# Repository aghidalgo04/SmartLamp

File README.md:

# SmartLamp: Embedded Environmental Control System

**SmartLamp** is a comprehensive embedded system designed to monitor study environments and automate lighting and ventilation. It integrates analog and digital sensors with real-time actuation, communicating via a custom UART protocol to a PC interface.

This project demonstrates a full-cycle embedded development process: **Requirements Engineering → SysML Architecture → Hardware Design (PCB) → Firmware Implementation.**

---

## Key Features

* **Real-time Environmental Monitoring:**
    * **Noise Level:** Analog sampling via microphone (categorized as Low/Medium/High) using **Timer 0** interrupts.
    * **Air Quality:** CO2 and TVOC monitoring via **iAQ-Core** (I2C).
    * **Lighting:** Ambient light sensing (Lux) via **VEML7700** (I2C).
    * **Climate:** Temperature and Humidity acquisition (Analog Sensors).
* **Intelligent Actuation:**
    * **Smart Lighting:** Addressable RGB LED strip (SK9822) controlled via **Software SPI** (Bit-banging).
    * **Active Cooling:** DC Fan speed control via **Hardware PWM** (Timer 2).
* **Connectivity:**
    * Robust **UART** communication protocol (9600 baud) with CRC checksums for data integrity.
    * Command-based interface for remote control and telemetry.

---

## Tech Stack & Tools

* **Microcontroller:** Microchip PIC16F886 (8-bit, 20MHz External Oscillator).
* **Firmware Development:** C Language, MPLAB X IDE, XC8 Compiler.
* **Hardware Design:** KiCad (Schematics & PCB Layout).
* **System Modeling:** Eclipse Papyrus (SysML for Block/Activity diagrams).
* **Protocols Implemented:** I2C (MSSP), SPI (Bit-banged), UART (EUSART), PWM (CCP1), ADC.

---

## Repository Structure

The project follows a structured engineering workflow separating development artifacts, documentation, and datasheets.

```text
SmartLamp/
├── Desarrollo/                    # Main Development Directory
│   ├── KiCad/                     # Hardware Design Source
│   │   ├── ProyectoSE.kicad_sch      # Electronic Schematics
│   │   └── ProyectoSE.kicad_pcb      # PCB Layout
│   │   
│   ├── MPLAB/                     # Firmware Source Code
│   │   ├── Code/                  # Application Logic
│   │   │   ├── main.c                # Main Loop & Interrupt Service Routines
│   │   │   └── [Test Files].c        # Unit tests for subsystems
│   │   │
│   │   └── Functions/             # Hardware Abstraction Layer (HAL)
│   │       ├── adc-v1.c/h            # Analog-to-Digital Converter Driver
│   │       ├── i2c-v2.c/h            # I2C Protocol Driver (Hardware MSSP)
│   │       ├── pwm-v1.c/h            # PWM Driver (Timer 2 + CCP)
│   │       ├── spi-master-v1.c/h     # SPI Driver (Software Implementation)
│   │       └── uart-v1.c/h           # UART Driver (Circular Buffer logic)
│   │
│   └── Papyrus/                   # System Architecture Models (UML/SysML)
│
├── Imde-comp/                     # PC Interface Software (Component)
├── Hojas técnicas-20251026/       # Component Datasheets (Sensors/MCU)
└── Documentación/                     # Project Documentation
```

---

## System Architecture

### 1. Firmware Architecture (HAL Approach)
The firmware is designed with modularity in mind. The `main.c` handles the high-level business logic and state management, while the `Functions/` folder contains reusable drivers that abstract the PIC16F886 hardware registers.

* **Interrupt-Driven Sampling:** Noise levels are sampled every 5ms using **Timer 0 (TMR0)** interrupts to ensure non-blocking operation.
* **State Machine:** The UART receiver utilizes a Finite State Machine (FSM) to parse incoming frames byte-by-byte, preventing buffer overflows and handling packet fragmentation.

### 2. Hardware Design (KiCad)
The hardware includes signal conditioning for analog sensors and logic level translation for the communication bus.
* **I2C Bus:** Pull-up resistors configured for 100kHz standard mode.
* **Power:** Regulated 5V rail for logic and separate rail for inductive loads (Fan).

---

## Communication Protocol

Communication between the SmartLamp and the PC is handled via a binary protocol with the following frame structure:

| Header | Length | Command | Payload | CRC (Dummy) |
|:------:|:------:|:-------:|:-------:|:-----------:|
| `0xAA` | 1 Byte | 1 Byte  | N Bytes |   2 Bytes   |

**Command Examples:**
* `0x04`: Set Fan Speed (Payload: 0-100%).
* `0x05`: Set LED Color (Payload: R, G, B, Intensity).
* `0x02`: Read CO2 Level (Response: ppm).

---

## Setup & Installation

### Prerequisites
* **MPLAB X IDE** (v5.xx or higher).
* **XC8 Compiler**.
* **KiCad** (v6.0 or higher) for hardware viewing.

### Build Instructions
1.  Clone the repository:
    ```bash
    git clone [https://github.com/aghidalgo04/SmartLamp.git](https://github.com/aghidalgo04/SmartLamp.git)
    ```
2.  Open **MPLAB X IDE** and import the project from `Desarrollo/MPLAB`.
3.  Ensure the device is set to **PIC16F886** and the toolchain to **XC8**.
4.  Build the project (`Production > Build Project`).
5.  Flash the `.hex` file using a **PICkit 3/4** programmer.

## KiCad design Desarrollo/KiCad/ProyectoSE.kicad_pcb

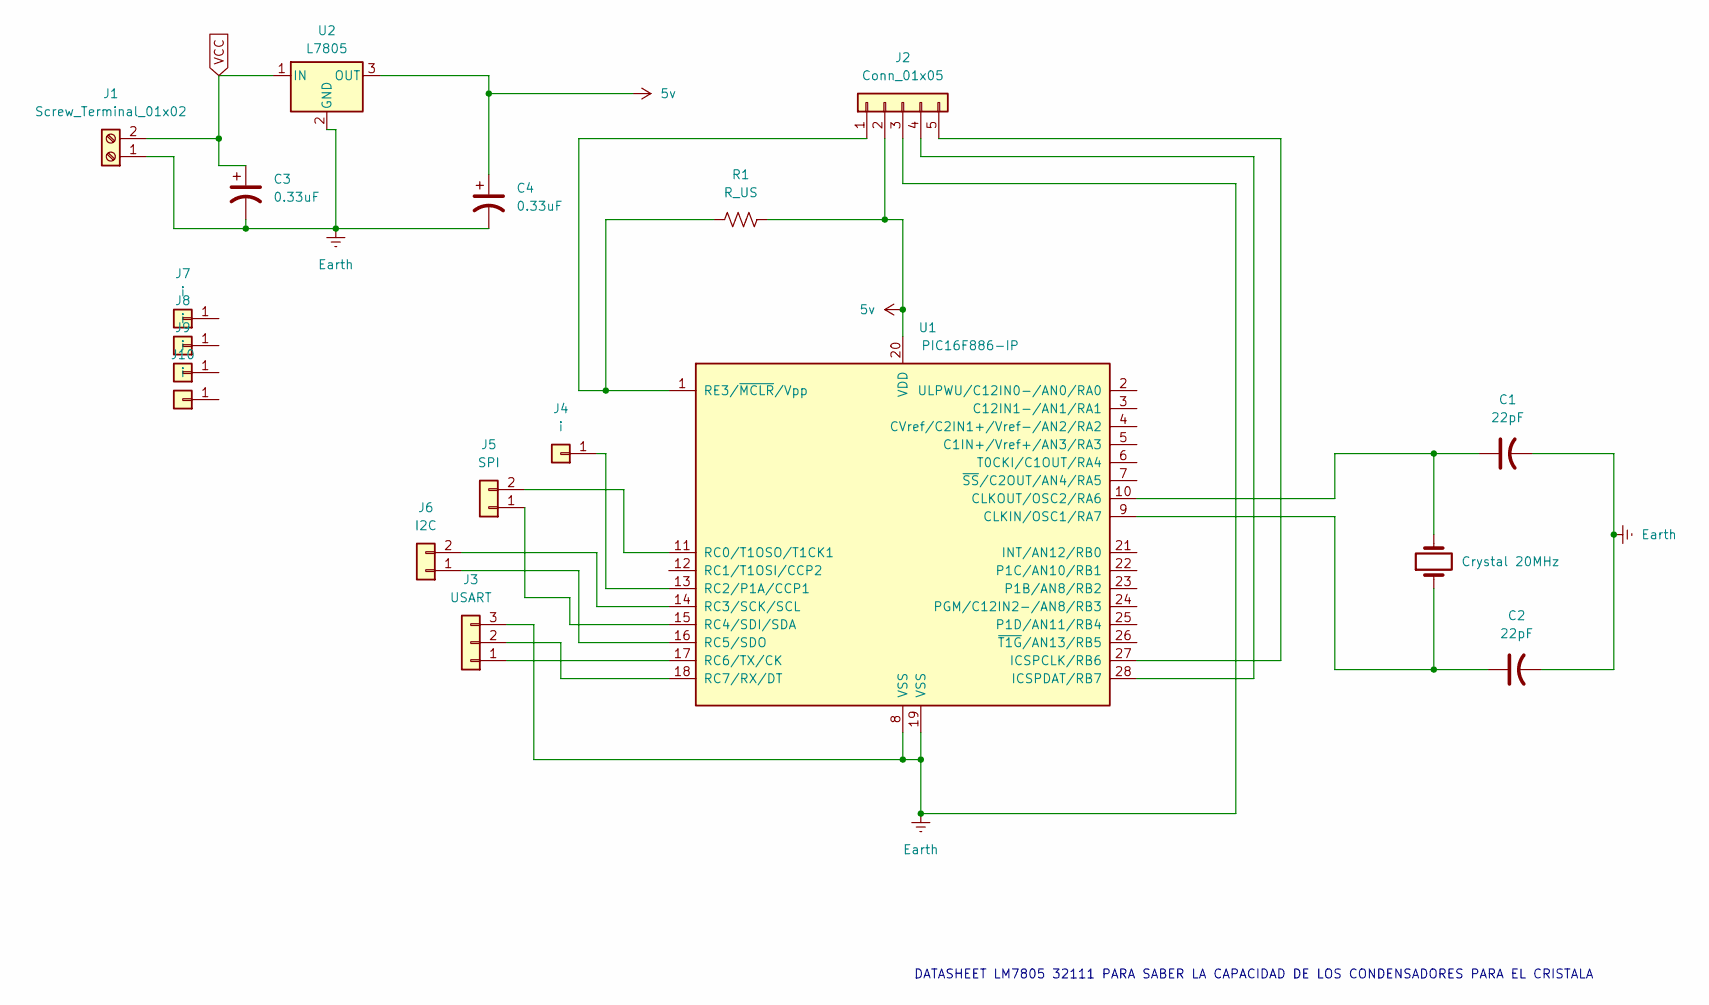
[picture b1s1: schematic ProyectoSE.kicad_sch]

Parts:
C1, C2: 22pF; C_Disc_D7.5mm_W5.0mm_P10.00mm
C3, C4: 0.33uF; C_Disc_D6.0mm_W4.4mm_P5.00mm
J1: Screw_Terminal_01x02; TerminalBlock_Phoenix_MKDS-1,5-2-5.08_1x02_P5.08mm_Horizont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
J2: Conn_01x05; PinHeader_1x05_P2.54mm_Vertical
J3: USART; PinHeader_1x03_P2.54mm_Vertical
J4: i; PinHeader_1x01_P2.54mm_Vertical
J5: SPI; PinHeader_1x02_P2.54mm_Vertical
J6: I2C; PinHeader_1x02_P2.54mm_Vertical
J7, J8, J9, J10: i; MountingHole_4mm_Pad
R1: R_US; R_Axial_DIN0204_L3.6mm_D1.6mm_P7.62mm_Horizontal
U1: PIC16F886-IP; DIP-28_W7.62mm
U2: L7805; TO-220-3_Vertical
Y1: Crystal 20MHz; Crystal_HC49-U_Vertical

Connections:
5v: C4.1, J2.2, R1.2, U1.20 (VDD), U2.3 (OUT)
Earth: C1.2, C2.2, C3.2, C4.2, J1.1, J2.3, J3.3, U1.8 (VSS), U1.19 (VSS), U2.2 (GND)
unnamed: J2.1, R1.1, U1.1 (RE3/~MCLR/Vpp)
unnamed: J2.4, U1.28 (ICSPDAT/RB7)
unnamed: J2.5, U1.27 (ICSPCLK/RB6)
unnamed: J3.1, U1.17 (RC6/TX/CK)
unnamed: J3.2, U1.18 (RC7/RX/DT)
unnamed: J4.1, U1.13 (RC2/P1A/CCP1)
unnamed: J5.1, U1.15 (RC4/SDI/SDA)
unnamed: J5.2, U1.11 (RC0/T1OSO/T1CK1)
unnamed: J6.1, U1.16 (RC5/SDO)
unnamed: J6.2, U1.14 (RC3/SCK/SCL)
unnamed: C2.1, U1.9 (CLKIN/OSC1/RA7), Y1.1
unnamed: C1.1, U1.10 (CLKOUT/OSC2/RA6), Y1.2
VCC: C3.1, J1.2, U2.1 (IN)

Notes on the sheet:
DATASHEET LM7805 32111 PARA SABER LA CAPACIDAD DE LOS CONDENSADORES PARA EL CRISTALA

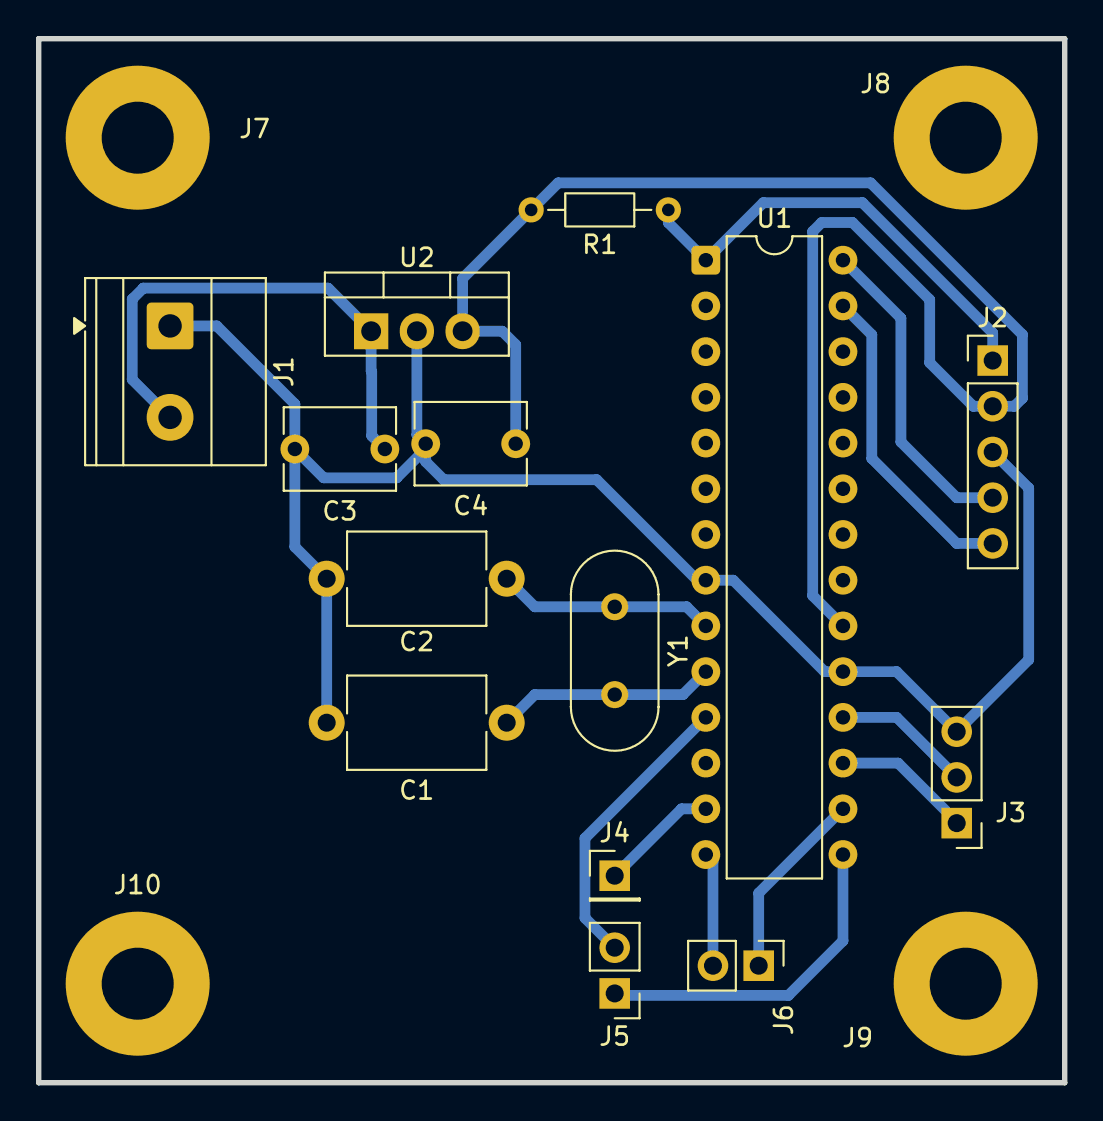
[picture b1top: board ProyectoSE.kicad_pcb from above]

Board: 2 copper layers, 57.0 x 58.0 mm, 18 parts (0 on the bottom side), 15 nets.

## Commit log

2026-01-03 Uploaded project to new github
2026-01-03 Uploaded documentation
